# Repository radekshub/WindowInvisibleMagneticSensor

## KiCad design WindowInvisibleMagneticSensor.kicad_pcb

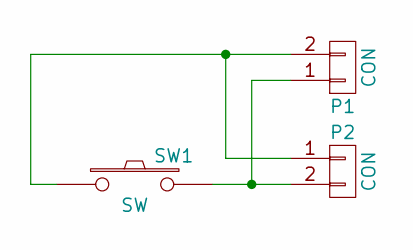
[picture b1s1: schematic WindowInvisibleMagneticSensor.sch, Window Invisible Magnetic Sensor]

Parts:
P1: CON; Socket_Strip_Angled_1x02_Pitch2.54mm
P2: CON; Pin_Header_Straight_1x02_Pitch2.54mm_SMD_Pin1Left
SW1: SW; R_Axial_DIN0411_L9.9mm_D3.6mm_P20.32mm_Horizontal

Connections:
unnamed: P1.1, P2.2, SW1.2
unnamed: P1.2, P2.1, SW1.1

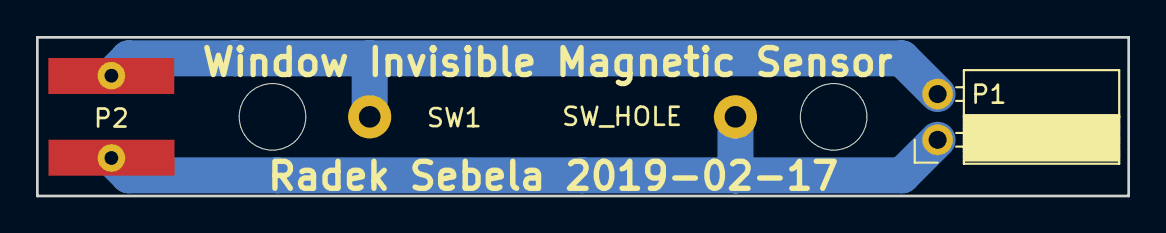
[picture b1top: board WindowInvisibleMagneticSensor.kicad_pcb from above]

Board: 2 copper layers, 60.6 x 8.8 mm, 4 parts (0 on the bottom side), 2 nets.

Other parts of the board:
SW_HOLE: M3; MountingHole_3mm

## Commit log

2019-02-24 Added files revision 1.0.
